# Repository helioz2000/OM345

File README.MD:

# OM345 replacement
This project (KiCad) is to replace the OM345 RF amlifier module found in various Marconi instruments such as the MI2955.

The project is based on the MAR-7+ from MiniCircuits.
Two different designs have been developed.

**WARNING:** At the writing of this document I have only just ordered the PCBs, actual performance and functionality is yet to be confirmed. 

## OM345A
This design is based on the reference circuit published in the MAR-7+ data sheet. 

Features:

- 2 resistors in parrallel to set the bias current.
- Pi attenuator pad on RF input for gain matching
- De-coupling capacitors on RF in and RF out

## OM345B
This minimal component design serves as a drop-in replacement for OM345s in the MI2955 RF generator (AA04 board). This board provides de-coupling capacitors and the circuit has an ALC to control the gain, so there is no need for exact gain matching of the replacement board and hence no need for a pad.

### Acknowledgement
I'd like to acknowledge the great community group **Marconi-Test-Instruments** located at [groups.io](https://groups.io/g/Marconi-Test-Instruments)
which have been an absolute fountain of knowledge and provided me with lots of help.

My other source of knowledge has come from RFMAN's [YouTube](https://www.youtube.com/@rfmanrfman4536) channel. He provides a lot of useful detail on repairing the MI2955.

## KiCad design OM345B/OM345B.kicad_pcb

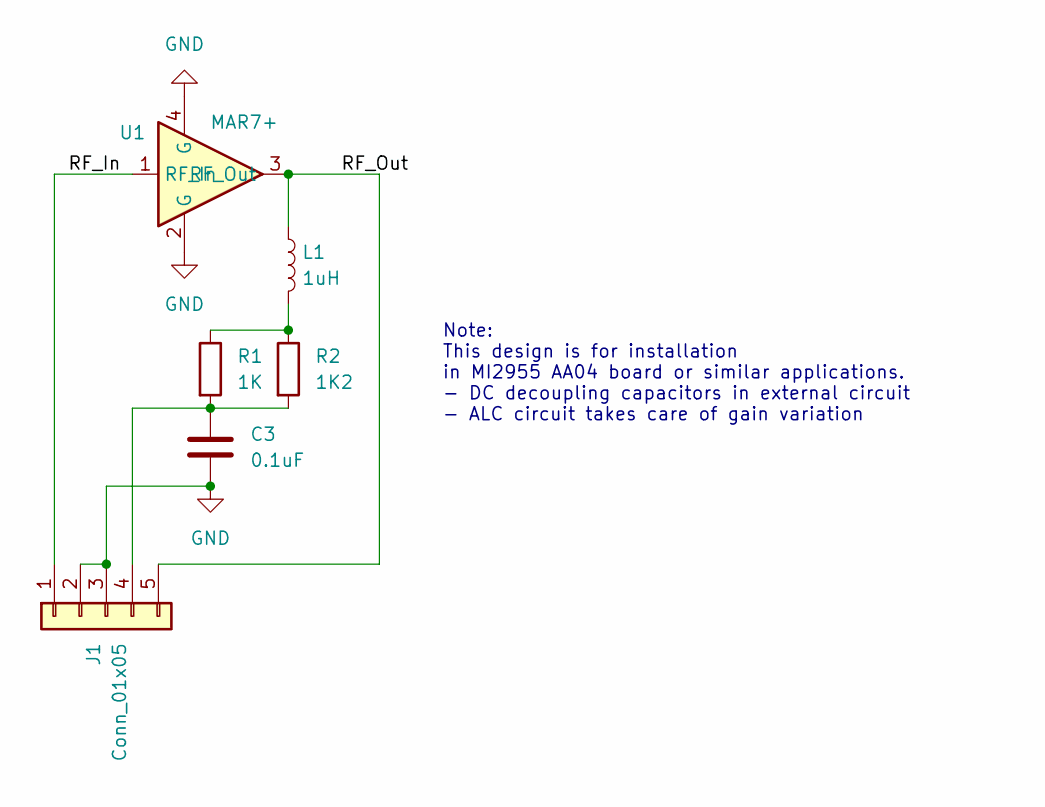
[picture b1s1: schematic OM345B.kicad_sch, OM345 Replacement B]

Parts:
C3: 0.1uF; C_0603_1608Metric_Pad1.08x0.95mm_HandSolder
J1: Conn_01x05; PinHeader_1x05_P2.54mm_Vertical
L1: 1uH; L_0603_1608Metric_Pad1.05x0.95mm_HandSolder
R1: 1K; R_0603_1608Metric_Pad0.98x0.95mm_HandSolder
R2: 1K2; R_0603_1608Metric_Pad0.98x0.95mm_HandSolder
U1: MAR7+; VV105

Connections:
/RF_In: J1.1, U1.1 (RF_In)
/RF_Out: J1.5, L1.1, U1.3 (RF_Out)
GND: C3.2, J1.2, J1.3, U1.2 (G), U1.4 (G)
unnamed: C3.1, J1.4, R1.2, R2.2
unnamed: L1.2, R1.1, R2.1

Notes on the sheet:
Note: This design is for installation in MI2955 AA04 board or similar applications. - DC decoupling capacitors in external circuit - ALC circuit takes care of gain variation

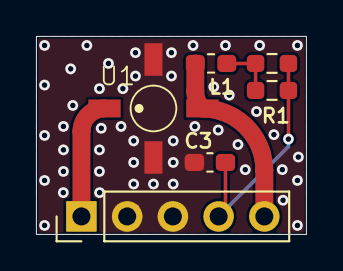
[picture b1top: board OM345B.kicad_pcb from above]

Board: 2 copper layers, 15.0 x 11.0 mm, 6 parts (0 on the bottom side), 5 nets.

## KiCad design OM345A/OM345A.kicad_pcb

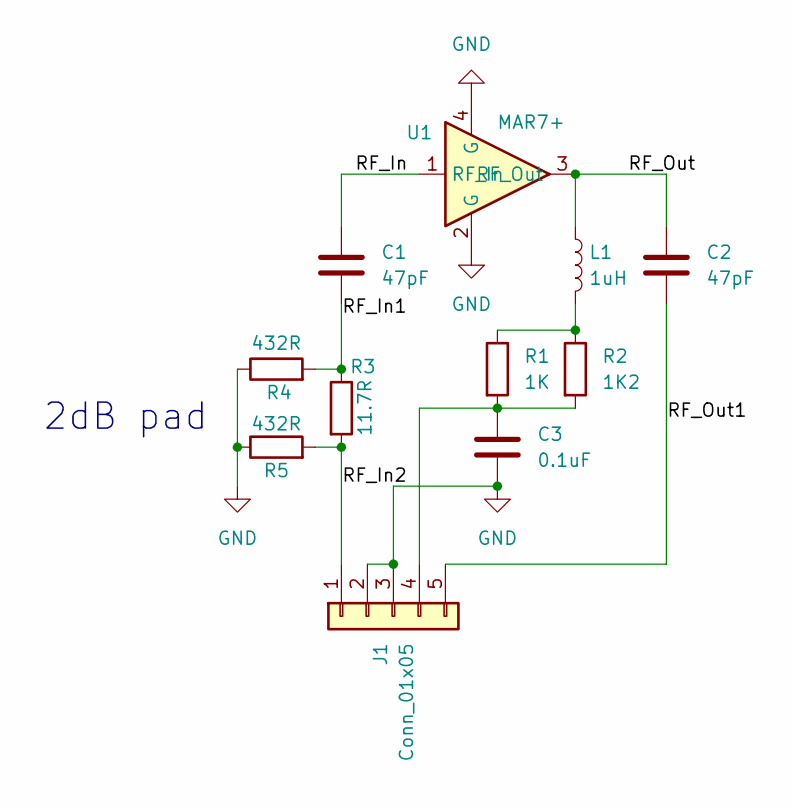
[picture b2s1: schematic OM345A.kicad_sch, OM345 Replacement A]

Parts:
C1, C2: 47pF; C_0603_1608Metric_Pad1.08x0.95mm_HandSolder
C3: 0.1uF; C_0603_1608Metric_Pad1.08x0.95mm_HandSolder
J1: Conn_01x05; PinHeader_1x05_P2.54mm_Vertical
L1: 1uH; L_0603_1608Metric_Pad1.05x0.95mm_HandSolder
R1: 1K; R_0603_1608Metric_Pad0.98x0.95mm_HandSolder
R2: 1K2; R_0603_1608Metric_Pad0.98x0.95mm_HandSolder
R3: 11.7R; R_0603_1608Metric_Pad0.98x0.95mm_HandSolder
R4, R5: 432R; R_0603_1608Metric_Pad0.98x0.95mm_HandSolder
U1: MAR7+; VV105

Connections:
/RF_In: C1.1, U1.1 (RF_In)
/RF_In1: C1.2, R3.1, R4.2
/RF_In2: J1.1, R3.2, R5.2
/RF_Out: C2.1, L1.1, U1.3 (RF_Out)
/RF_Out1: C2.2, J1.5
GND: C3.2, J1.2, J1.3, R4.1, R5.1, U1.2 (G), U1.4 (G)
unnamed: C3.1, J1.4, R1.2, R2.2
unnamed: L1.2, R1.1, R2.1

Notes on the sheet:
2dB pad

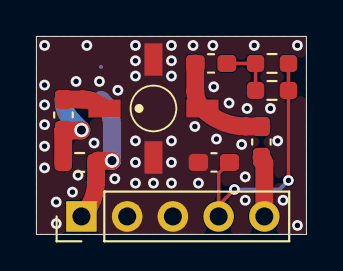
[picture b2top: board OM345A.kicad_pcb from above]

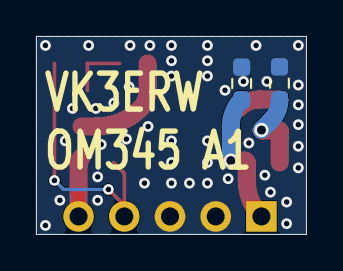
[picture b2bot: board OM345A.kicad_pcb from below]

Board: 2 copper layers, 15.0 x 11.0 mm, 11 parts (2 on the bottom side), 8 nets.
